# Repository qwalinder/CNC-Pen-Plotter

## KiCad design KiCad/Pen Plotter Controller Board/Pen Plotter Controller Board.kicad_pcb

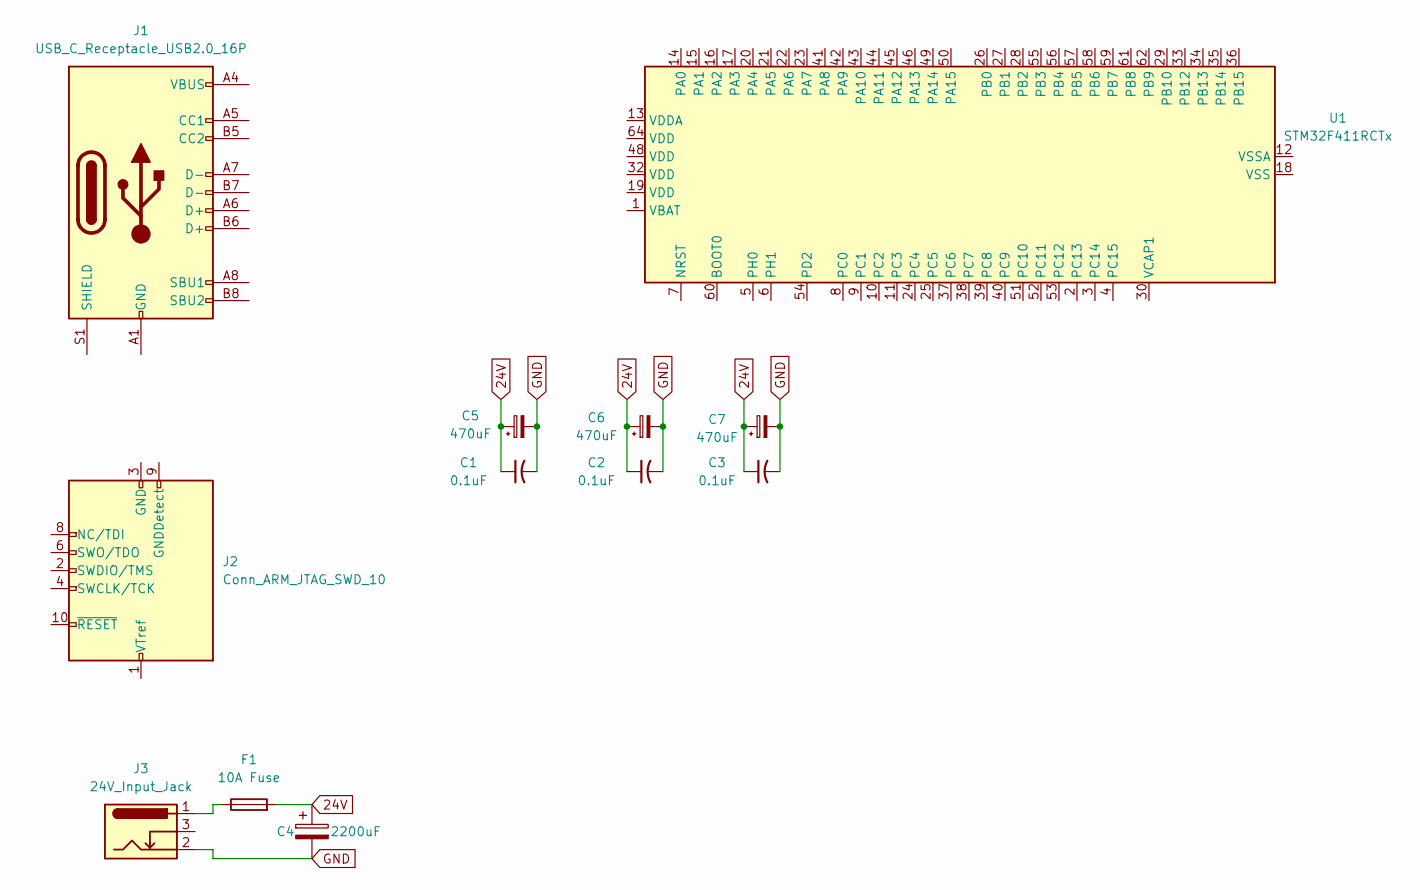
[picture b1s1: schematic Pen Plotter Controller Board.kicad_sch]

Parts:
C1, C2, C3: 0.1uF; C_Rect_L7.0mm_W2.0mm_P5.00mm
C4: 2200uF; CP_Radial_D13.0mm_P7.50mm
C5, C6, C7: 470uF; CP_Radial_D8.0mm_P3.80mm
F1: 10A Fuse; Fuse_Blade_ATO_directSolder
J1: USB_C_Receptacle_USB2.0_16P; USB_C_Receptacle_GCT_USB4085
J2: Conn_ARM_JTAG_SWD_10; PinHeader_2x05_P1.27mm_Horizontal
J3: 24V_Input_Jack; BarrelJack_Tensility_54-00166
U1: STM32F411RCTx; LQFP-64_10x10mm_P0.5mm

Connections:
24V: C1.1, C2.1, C3.1, C4.1, C5.1, C6.1, C7.1, F1.2
GND: C1.2, C2.2, C3.2, C4.2, C5.2, C6.2, C7.2, J3.2
unnamed: F1.1, J3.1
unnamed: J1.A1 (GND), J1.A12 (GND), J1.B1 (GND), J1.B12 (GND)
unnamed: J1.A4 (VBUS), J1.A9 (VBUS), J1.B4 (VBUS), J1.B9 (VBUS)
unnamed: J2.3 (GND), J2.5 (GND)
unnamed: U1.18 (VSS), U1.31 (VSS), U1.47 (VSS), U1.63 (VSS)

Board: 2 copper layers, 12 parts (0 on the bottom side), 7 nets, no tracks yet.

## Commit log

2025-08-28 Initial Commit - beginnings of PCB schematic layout/design
